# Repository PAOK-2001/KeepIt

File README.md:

# System Overview

The present system is intended as a demonstrator of how to apply computer vision techniques for autonomous driving. In particular, we tackle the matter of lane detection and following.

To deploy the image processing we will use a _Raspberry Pi 4B_ which will run the OpenCv script that finds the lanes and computes the center; it will also calculate the offset between said center and the center of the camera, returning an error (measured in pixels). The systems for moving and steering the car are controlled by a _Raspberry Pi Pico_, running FreeRTOS. The micro-controller will read the error by I2C and apply a proportional control loop (tunned using the Ziegler-Nichols experimental method) to correct the direction using the steering. 

Current and voltage sensors for a stable functioning of the system; a low-pass filter was implemented to rule out any current peaks and only stop the system when current to the motors consistently rises as a result of motor stall.

The system is summarized in the following diagram.

# Lane Detector
## Methodology
The focus of this project was to create a lane detector class for future implementation in lane keep. The approach for detecting the lanes consisted in finding the edges present in the image using gradient difference (Canny); then masking the image to only include the area corresponding to the road, upon which Hough Transform was applied, detecting probable lines in the image. A linear regression was obtained for each line, which allowed the classification into right (positive slope) and left (negative slope) boundaries; finally, the average coefficients  were found for each boundary, which described the average lines that delimited the lane.  

## Theoretical Background
### Hough Transform
Represents points as lines in Hough space, where the axis represents the values of a linear equation corresponding to a line that goes through that point . In particular, Hough transform uses the polar representation of a line      &rho;= Acos(&theta;)+Bcos(&theta;) where the axes are &rho; and &theta;.

For multiple points, Hough Transform detects the area in Hough space with the
most number of interceptions, returning the most probable values of the linear equation describing the collection of points. In OpenCV this is implemented as HoughLinesP, and returns the cartesian coordinates of the detected line in a vector of 4 integers Vec4i {x1,y1,x2,y1}.

### Canny Edge Detection

Canny is an algorithm that uses various states to detect the edge lines in an image. Firstly it applies a Gaussian Blur to the matrix of pixels to eliminate noise within the image. 
    
Then it uses the Sobel operator to calculate the pixel gradient in all directions. for those gradients Canny’s algorithm looks for those who are bigger than their neighbors, returning a thin edge line. 

## Lane Detector Object

    class laneDetector{
        private:
            // Images states used in lane detection
            Mat edgeImg, lineImg;
            // Lane lines in the format of a 4 integer vector such as  (x1, y1, x2, y2), 
            Vec4i leftLine, rightLine;
            // Coordinate that represents the senter of given lane
            Point center;
            // Auxiliary functions
            static pair<float,float> linearFit(Vec4i lineCoordinates); 
            static float averageCoheficient(vector<float> registeredCoheficients);
            static Vec4i makeCoordinate(float slope, float intercept, int imgHeight);

        public:
            laneDetector();
            void loadFrame(Mat cameraFrame);
            void findLanes();
            void findCenter();
            void display(Mat cameraFrame);
    };
### Class Composition
#### Atributes
| Atribute | Description |
| --- | ----- |
| edgeIMG | Pixel matrix that stores the Canny version of the loaded frame.  |
| lineIMG | Pixel matrix that stores the drawed lines and center point that will blended with the orignal image in the final display.  |
| leftLine, rightLine | A Vec4i structure that stores the coordinates of the endpoints of the respective lines that delimit the lane. Format: {x1, y1, x2, y2}|
|center|Point object that stores the coordinates for the center of the lanes|
#### Methods
##### Static
|Method| Description  |
| --- | ----- |
|linearFit(Vec4i lineCoordinates)|Takes a vector of 4 integers representing the endpoints of a line and returns the slope and intercept as a pair.|
|averageCoheficient(vector<float> registeredCoheficients)|Takes a vector of coheficients and returns the average value.|
|makeCoordinate(float slope, float intercept, int imgHeight)|Takes the coheficients of a linear equation and the height of the image and calcultates the coordinates of a a line.|
##### Non-Static
|Method| Description  |
| --- | ----- |
|void loadFrame(Mat cameraFrame) | Loads the image where the lanes wish to be found. It applies converts it to grayscale, and applies Canny Edge Detection, storing the result in *edgeIMG*.|
|void findLanes()| It makes mask using polygons to isolate the area where the road is, updating *edgeIMG*. Once the region on interest is obtained Hough Transform is used to detect the lines present; afterwards the **linearFit** method is used to find the slope and intercept for each line. Based on the slope, the lines are categorized into right and left boundaries. Finally, it finds the average lines for each side using **averageCoheficient** and it makes the endpoint coordinates (using **makeCoordinates**) to store them in *rightLine* and *leftLine*. It draws said lines on *lineIMG*|
|void findCenter()|Finds the center of the lane using the coordinates stored in *rightLine* and *leftLine*. Draws the center as a circle in *lineIMG*|
|void display(Mat cameraFrame) | Overlays the *lineIMG* on the real fram captured by the camera. |

# Implementaion
The Lane Detector can be used to find lanes in a single image or a video (read from a file or camera.)

**Still image:**

    laneDetector lanes;
    frame = imread("imageName");
    lanes.loadFrame(frame);
    lanes.findLanes();
    lanes.findCenter();
    lanes.display(frame);

**Camera:**

    VideoCapture dashCam(path);
    for (;;){
        dashCam.read(frame);
        lanes.loadFrame(frame);
        lanes.findLanes();
        lanes.findCenter();
        lanes.display(frame);
        if(waitKey(5)== 27){
            break;
        }
    }

# CAD DESIGN

## Base and Steering

For this project we decided to laser cut a custom base to build the model car upon; we designed it using SolidWorks and leaving the necessary holes for mounting the electrical system. A custom shroud was also built to mount the web cam on the front of the car.

For controlling the direction of the model, we implemented a simplified version of _Ackermann Steering_ which is controlled using a servo motor. 

Finished prototype             | View of Ackermann Steering
:-------------------------:|:-------------------------:
  |   

## Electrical

For a secure connection a breakout board was made to map the GPIO pins using screw terminals. A power breakout board was also designed for a 4 cells 18650 BMS; however, due to a faulty BMS it was not used in the final implementation.
GPIO Breakout Board             | BMS Breakout Board
:-------------------------:|:-------------------------:
  |   

### Demo Reel: 

https://www.youtube.com/watch?v=GjENCYGIipA&ab_channel=AbrahamDeAlbaFranco

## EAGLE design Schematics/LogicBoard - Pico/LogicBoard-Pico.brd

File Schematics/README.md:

### Appendix: GPIO Breakout Board
_I2C0_
- GP4 (I2C0_SDA)
- GP5 (I2CO_SCL)

_I2C1_
- GP21 (I2C1_SDA)
- GP20(I2C1_SCL)
_UART COMMUNICATION_ 
- GP0
- GP1

_H-BRIDGE (PWM):_
- Motor1: GP15, GP14
- Motor2: GP13, GP12

_SERVO:_
- GP11

_ALIMENTATION_
- +:  VSYS [40]
- GND: [38]

_VOLTAGE SENSOR (ADC)_
- GP28

_CURRENT SENSORS (ADC)_
- SENSOR1: GP27
- SENSOR2: GP26

_GENERAL PURPOSE_:
- GP8
- G99
- GP17

### POWER

- 5V:  x7
- 3.3V: x7
- 12V: x3
- GND: x7

# Photos

_Acknowlegment:_ Special thanks to [John Corrado (@CorradoCorrado)](https://github.com/CorradoCorrado) for his guidance on the design and manufacturing of the boards!

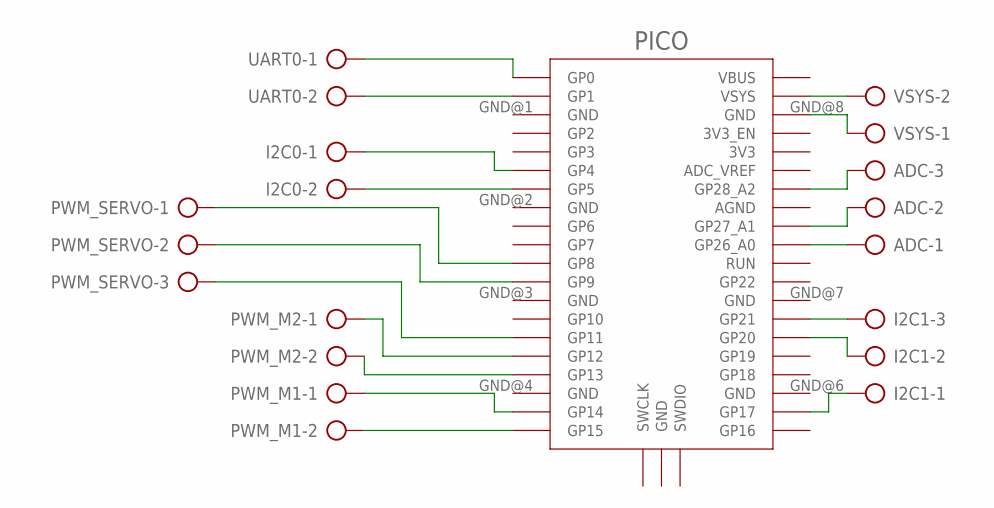
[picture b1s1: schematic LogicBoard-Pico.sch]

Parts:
ADC: AK500/3
I2C0: AK500/2
I2C1: AK500/3
PICO: RPI_PICO_IG-TH; RPI_PICO_TH
PWM_M1, PWM_M2: AK500/2
PWM_SERVO: AK500/3
UART0: AK500/2
VSYS: AK500/2

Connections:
unnamed: PICO.GND@8 (GND), VSYS.1
unnamed: PICO.VSYS, VSYS.2
unnamed: ADC.3, PICO.GP28_A2
unnamed: ADC.2, PICO.GP27_A1
unnamed: ADC.1, PICO.GP26_A0
unnamed: I2C1.3, PICO.GP21
unnamed: I2C1.2, PICO.GP20
unnamed: PICO.GP0, UART0.1
unnamed: PICO.GP1, UART0.2
unnamed: I2C0.1, PICO.GP4
unnamed: I2C0.2, PICO.GP5
unnamed: PICO.GP15, PWM_M1.2
unnamed: PICO.GP14, PWM_M1.1
unnamed: PICO.GP13, PWM_M2.2
unnamed: PICO.GP12, PWM_M2.1
unnamed: PICO.GP11, PWM_SERVO.3
unnamed: PICO.GP9, PWM_SERVO.2
unnamed: PICO.GP8, PWM_SERVO.1
unnamed: I2C1.1, PICO.GP17

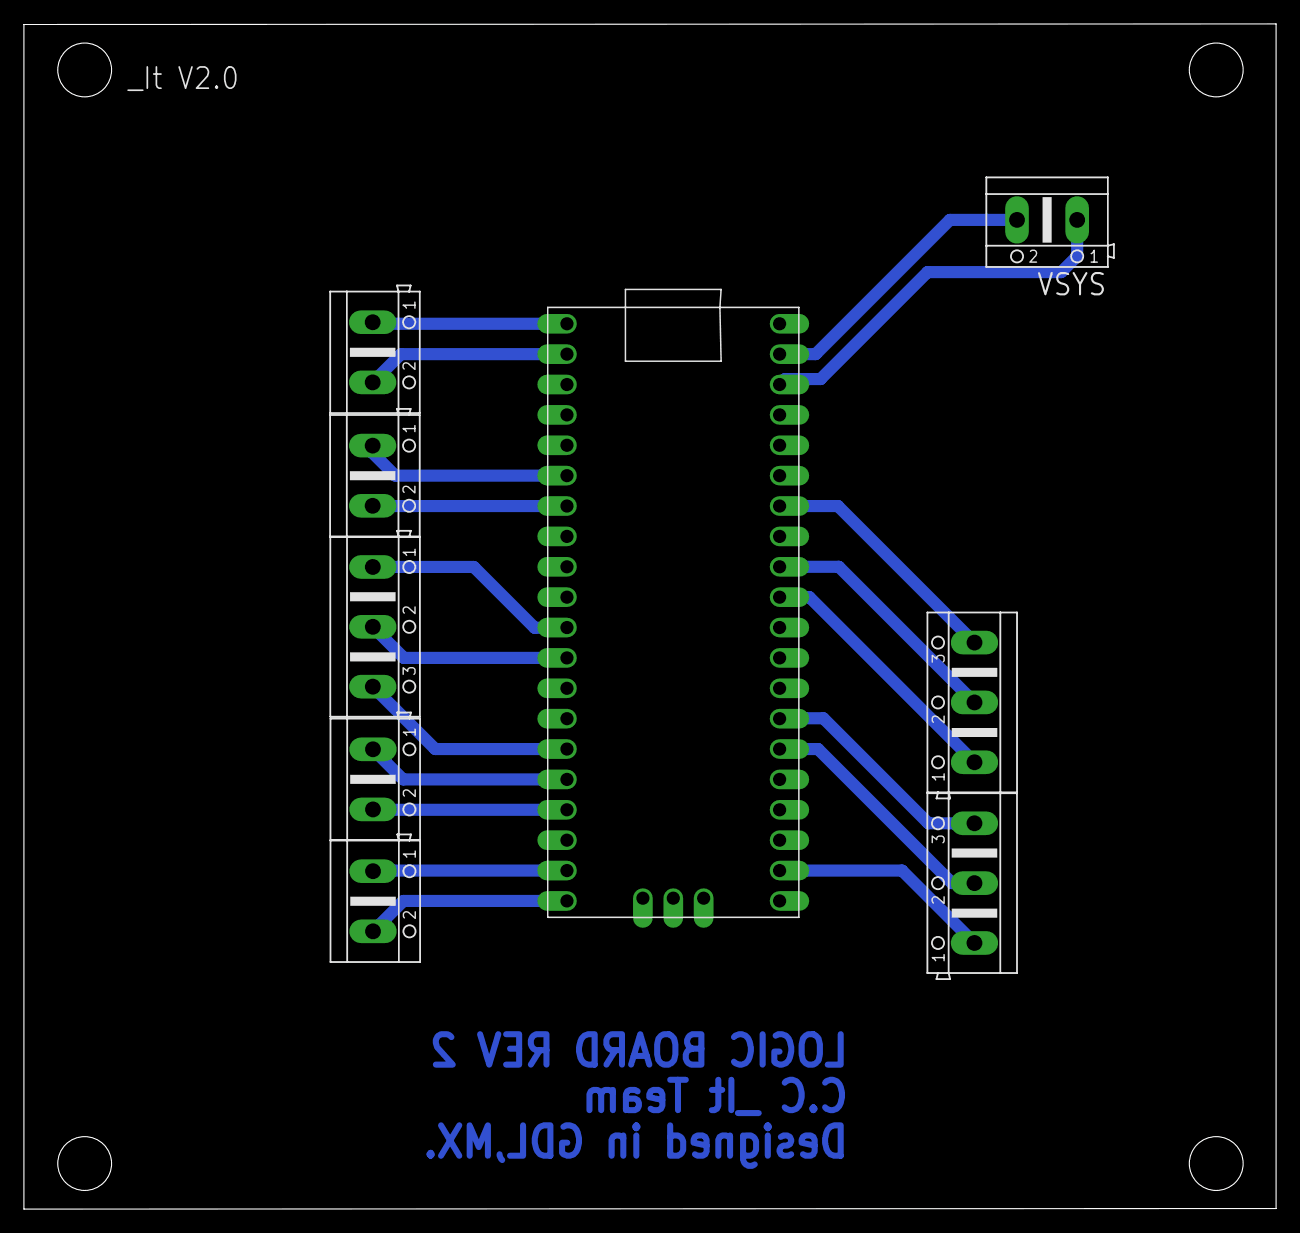
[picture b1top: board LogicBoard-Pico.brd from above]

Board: 2 copper layers, 104.7 x 99.1 mm, 9 parts (0 on the bottom side), 19 nets.

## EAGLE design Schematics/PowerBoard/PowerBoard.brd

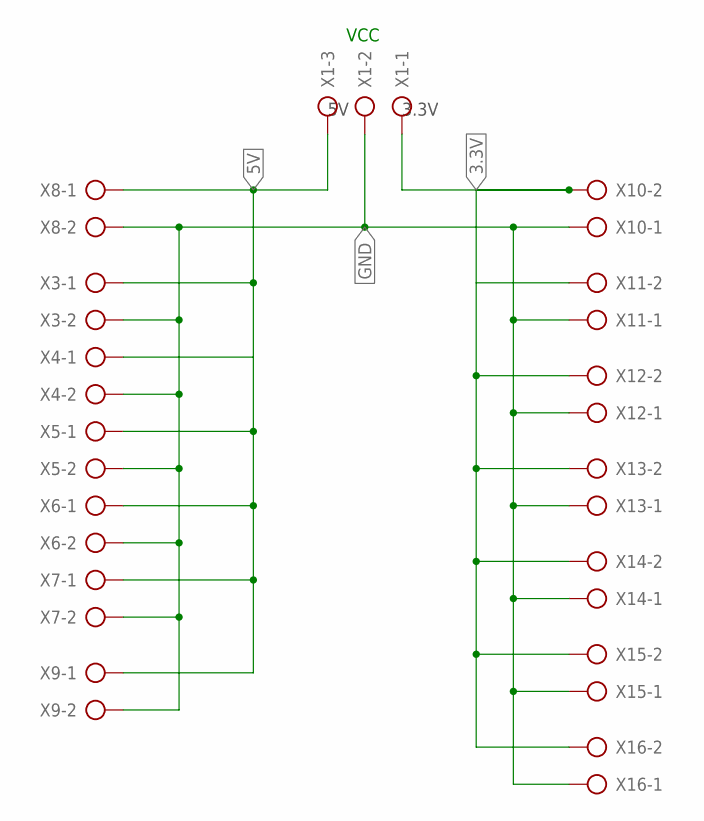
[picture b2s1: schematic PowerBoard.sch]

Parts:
X1: AK500/3
X3, X4, X5, X6, X7, X8, X9, X10, X11, X12, X13, X14, X15, X16: AK500/2

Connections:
3.3V: X1.1, X10.2, X11.2, X12.2, X13.2, X14.2, X15.2, X16.2
5V: X1.3, X3.1, X4.1, X5.1, X6.1, X7.1, X8.1, X9.1
GND: X1.2, X3.2, X4.2, X5.2, X6.2, X7.2, X8.2, X9.2, X10.1, X11.1, X12.1, X13.1, X14.1, X15.1, X16.1

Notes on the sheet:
VCC
3.3V

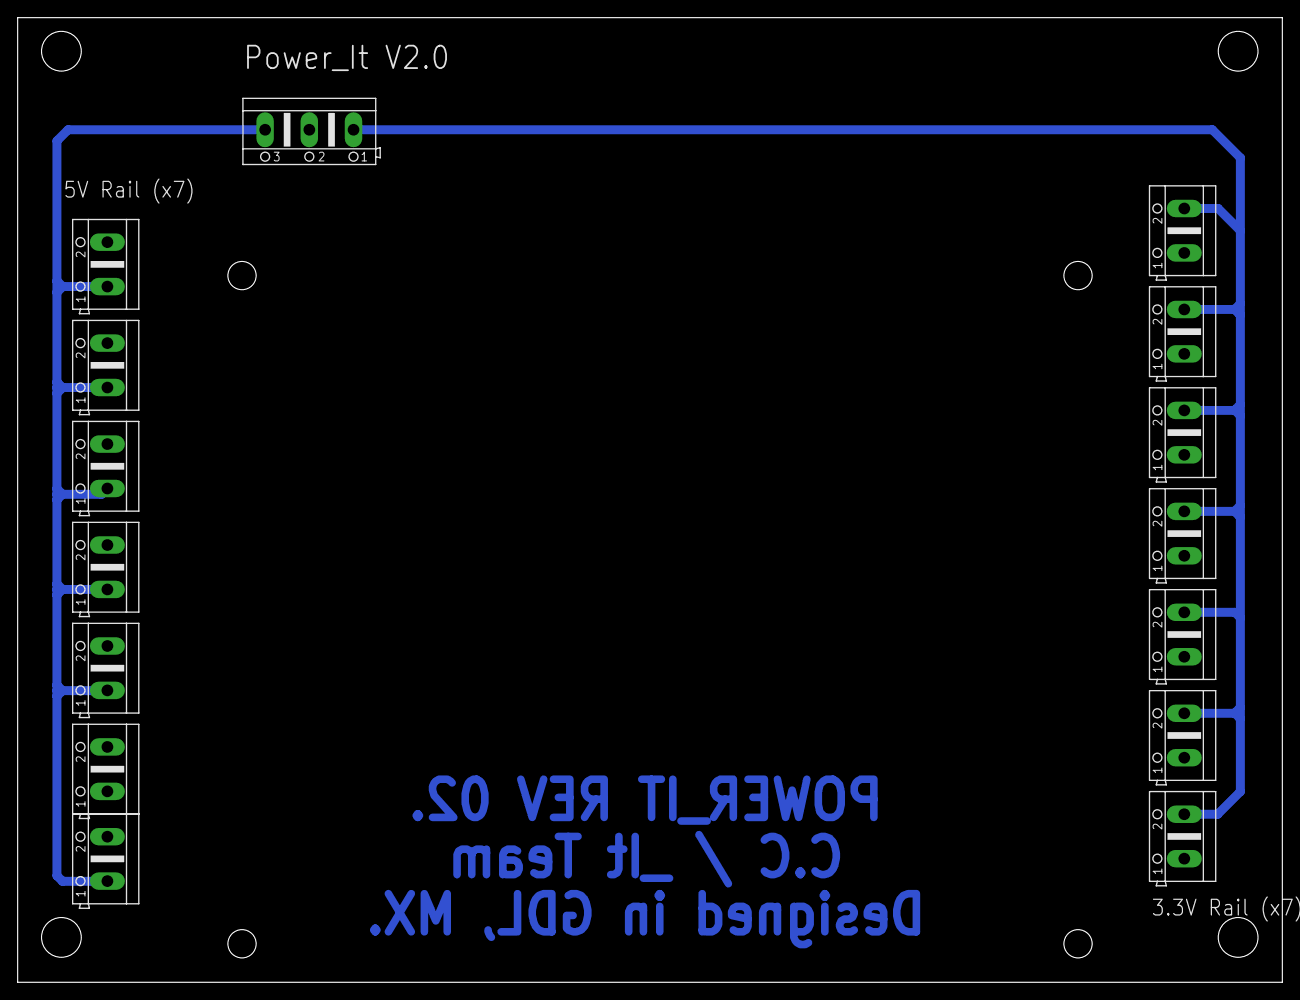
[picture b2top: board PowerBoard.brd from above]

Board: 2 copper layers, 143.2 x 109.2 mm, 15 parts (0 on the bottom side), 3 nets.

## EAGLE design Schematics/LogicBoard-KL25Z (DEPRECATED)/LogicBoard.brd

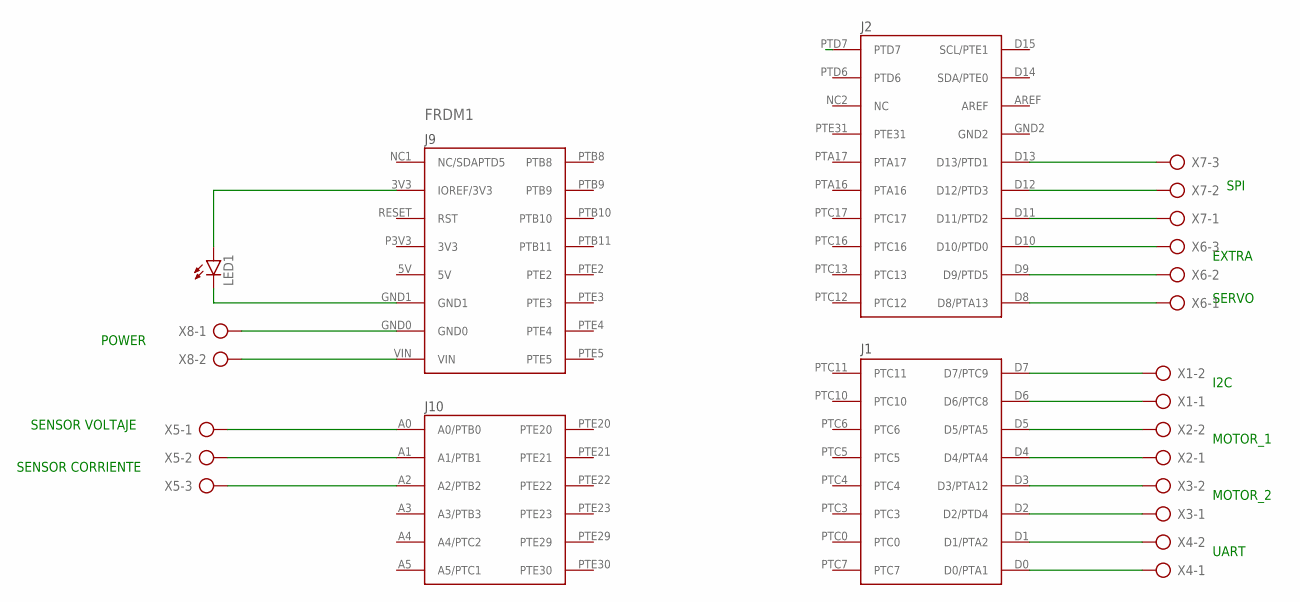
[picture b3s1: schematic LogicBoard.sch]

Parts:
FRDM1: FRDM-KL25ZNORMAL; FRDM_KL25Z_NORMAL
LED1: LED5MM
X1, X2, X3, X4, X8: AK500/2
X5, X6, X7: AK500/3

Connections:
unnamed: FRDM1.D7 (D7/PTC9), X1.2
unnamed: FRDM1.D6 (D6/PTC8), X1.1
unnamed: FRDM1.D5 (D5/PTA5), X2.2
unnamed: FRDM1.D4 (D4/PTA4), X2.1
unnamed: FRDM1.D3 (D3/PTA12), X3.2
unnamed: FRDM1.D2 (D2/PTD4), X3.1
unnamed: FRDM1.D1 (D1/PTA2), X4.2
unnamed: FRDM1.D0 (D0/PTA1), X4.1
unnamed: FRDM1.GND0, X8.1
unnamed: FRDM1.VIN, X8.2
unnamed: FRDM1.A0 (A0/PTB0), X5.1
unnamed: FRDM1.A1 (A1/PTB1), X5.2
unnamed: FRDM1.A2 (A2/PTB2), X5.3
unnamed: FRDM1.D8 (D8/PTA13), X6.1
unnamed: FRDM1.D9 (D9/PTD5), X6.2
unnamed: FRDM1.D10 (D10/PTD0), X6.3
unnamed: FRDM1.D11 (D11/PTD2), X7.1
unnamed: FRDM1.D12 (D12/PTD3), X7.2
unnamed: FRDM1.D13 (D13/PTD1), X7.3
unnamed: FRDM1.GND1, LED1.K (C)
unnamed: FRDM1.3V3 (IOREF/3V3), LED1.A

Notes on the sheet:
I2C
UART
MOTOR_1
MOTOR_2
POWER
SENSOR VOLTAJE
SENSOR CORRIENTE
SERVO
EXTRA
SPI

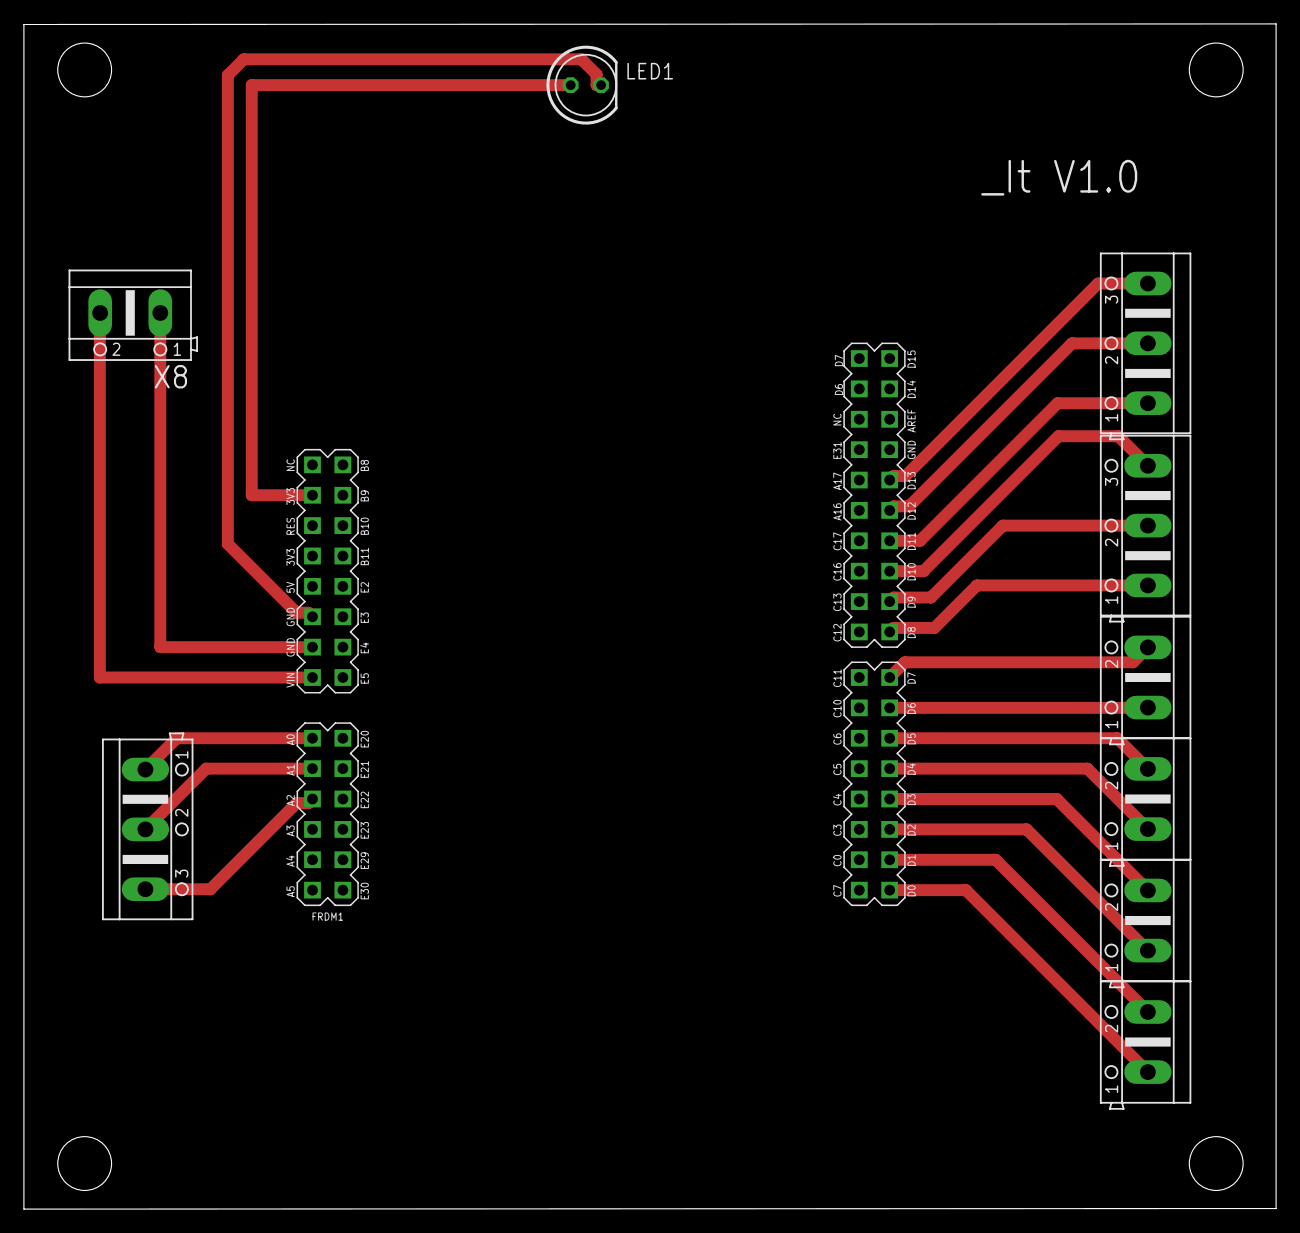
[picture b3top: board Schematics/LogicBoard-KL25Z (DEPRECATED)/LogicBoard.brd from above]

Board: 2 copper layers, 104.7 x 99.1 mm, 10 parts (0 on the bottom side), 21 nets.

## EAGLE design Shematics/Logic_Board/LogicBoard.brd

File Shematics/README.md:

# PINOUT: KEEP_IT

## LOGIC
_I2C0_
- GP4 (I2C0_SDA)
- GP5 (I2CO_SCL)

_I2C1_
- GP21 (I2C1_SDA)
- GP20(I2C1_SCL)
_UART COMMUNICATION_ 
- GP0
- GP1

_H-BRIDGE (PWM):_
- Motor1: GP15, GP14
- Motor2: GP13, GP12

_SERVO:_
- GP11

_ALIMENTATION_
- +:  VSYS [40]
- GND: [38]

_VOLTAGE SENSOR (ADC)_
- GP28
_CURRENT SENSORS (ADC)_
- SENSOR1: GP27
- SENSOR2: GP26

_GENERAL PURPOSE_:
- GP8
- G99
- GP17

## POWER
- 5V:  x7
- 3.3V: x7
- 12V: x3
- GND: x7

_#Note:_ This pinout is in regard the Raspberry Pi Pico version, as the KL25Z board is no longer employed,

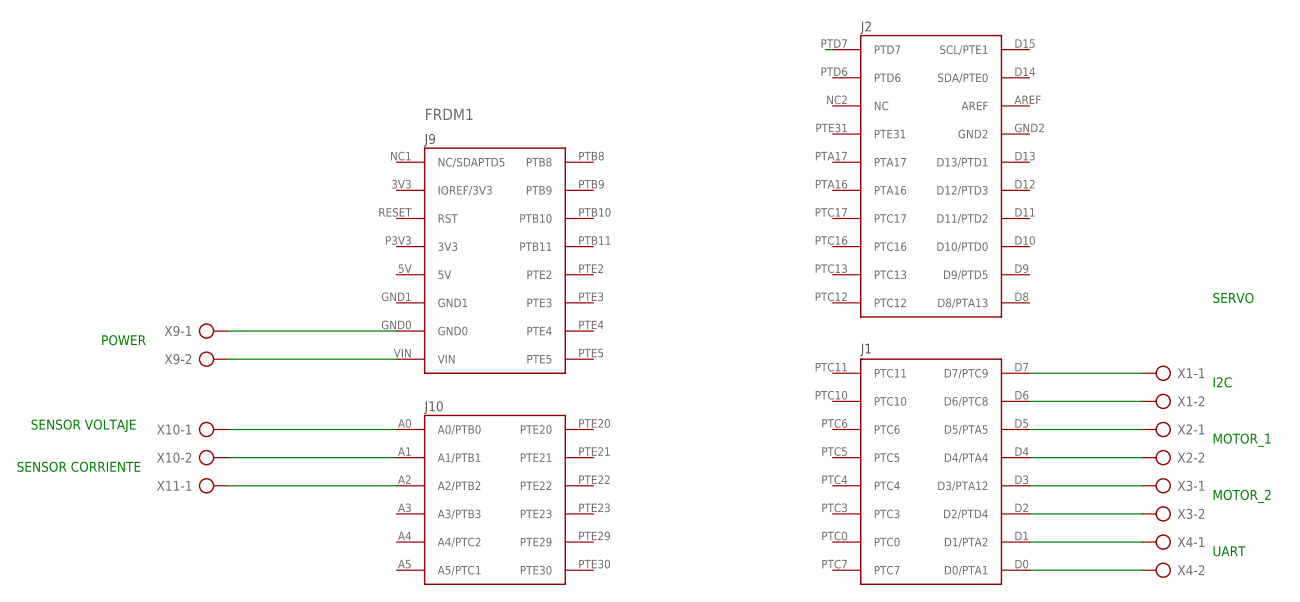
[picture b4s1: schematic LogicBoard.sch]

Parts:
FRDM1: FRDM-KL25ZNORMAL; FRDM_KL25Z_NORMAL
X1, X2, X3, X4, X9, X10, X11: AK500/2-H

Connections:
unnamed: FRDM1.D7 (D7/PTC9), X1.1
unnamed: FRDM1.D6 (D6/PTC8), X1.2
unnamed: FRDM1.D5 (D5/PTA5), X2.1
unnamed: FRDM1.D4 (D4/PTA4), X2.2
unnamed: FRDM1.D3 (D3/PTA12), X3.1
unnamed: FRDM1.D2 (D2/PTD4), X3.2
unnamed: FRDM1.D1 (D1/PTA2), X4.1
unnamed: FRDM1.D0 (D0/PTA1), X4.2
unnamed: FRDM1.VIN, X9.2
unnamed: FRDM1.GND0, X9.1
unnamed: FRDM1.A0 (A0/PTB0), X10.1
unnamed: FRDM1.A1 (A1/PTB1), X10.2
unnamed: FRDM1.A2 (A2/PTB2), X11.1

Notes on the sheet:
I2C
UART
MOTOR_1
MOTOR_2
POWER
SENSOR VOLTAJE
SENSOR CORRIENTE
SERVO

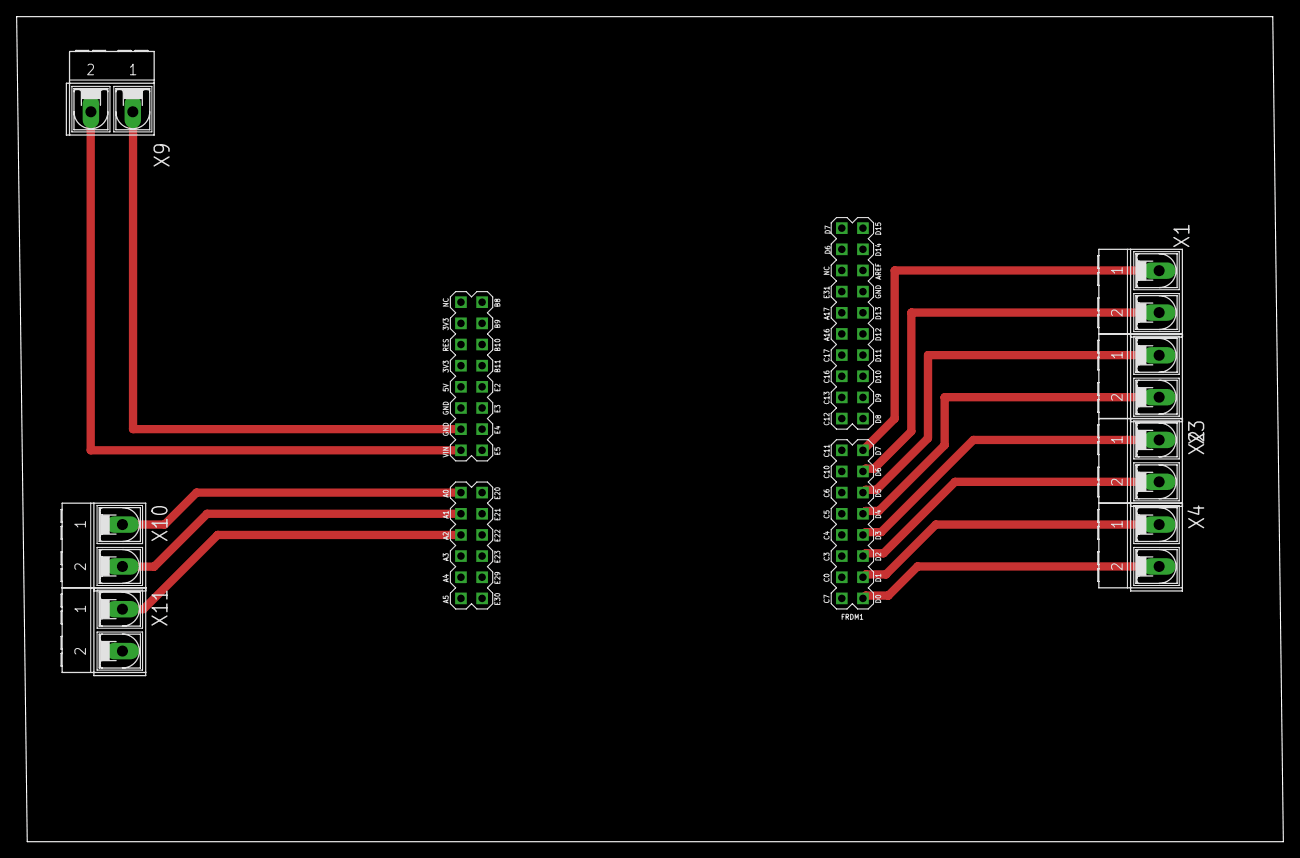
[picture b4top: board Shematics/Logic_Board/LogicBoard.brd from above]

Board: 2 copper layers, 152.1 x 99.0 mm, 8 parts (0 on the bottom side), 13 nets.

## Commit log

2022-09-28 Removed mask and change feed from video to camera
2022-09-28 Removed sample videos
2022-09-29 First attempt at color masking
2022-09-29 Deleted binary
2022-09-29 Fixed variable name
2022-09-29 Framerate and resolution change
2022-10-01 Added color filtering and slope discrimination
2022-10-01 minor changes
2022-10-01 Changed resolution for better performance and modified lane detection parameters
2022-10-01 Further adjusted lane recognition parameters
2022-10-26 Implemented calculation for displacement from center
2022-10-31 Added board schematic
2022-10-31 Modified GitIgnore
2022-10-31 Cleaned aux files
2022-11-01 Refactored logic board & completed power distribution board
2022-11-10 Updated Schematics
2022-11-10 Created Pico project template
2022-11-10 First Rasp Pico compilation attempt
2022-11-11 Pico build attempt #2 (seems to work)
2022-11-11 Implemented FreeRTOS file structure
2022-11-11 First draft of I2C communication
2022-11-11 Added RTOS tasks and main structure
2022-11-11 Implemented basic motor and servo tasks
2022-11-12 Testing I2C
2022-11-13 Implemented setup in I2C task
2022-11-14 Finished initial I2C setup in rtos task
2022-11-14 Implemented read error from Raspberry Pi 4B, over I2C.
2022-11-14 Formatting
2022-11-14 Send lane error to Pico with I2C
2022-11-16 Refactored Power PCB
2022-11-16 Refactored logic board
2022-11-19 Servo draft
2022-11-19 Fixed formatiing
2022-11-19 Added PWM control for drivetrain, Tuned servo limits
2022-11-21 Added fail safe to avoid system exeeceding limits
2022-11-21 Added prints for debugging purposes
2022-11-21 Implemented proportional control loop
2022-11-21 Changed servo left limit and added an isReceiving flag
2022-11-21 Added video recording in raspberry pi
2022-11-21 Added recording
2022-11-22 Implemented DSP filter and current overload handle
2022-11-22 Added video recording from Raspberry pi's POV
2022-11-26 Current filter calibration
2022-11-30 Added 3D design files
2022-12-01 Merged missing branches and updated README

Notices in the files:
parts and their libraries:
SparkFun-Capacitors: Licensing: Creative Commons ShareAlike 4.0 International - https://creativecommons.org/licenses/by-sa/4.0
